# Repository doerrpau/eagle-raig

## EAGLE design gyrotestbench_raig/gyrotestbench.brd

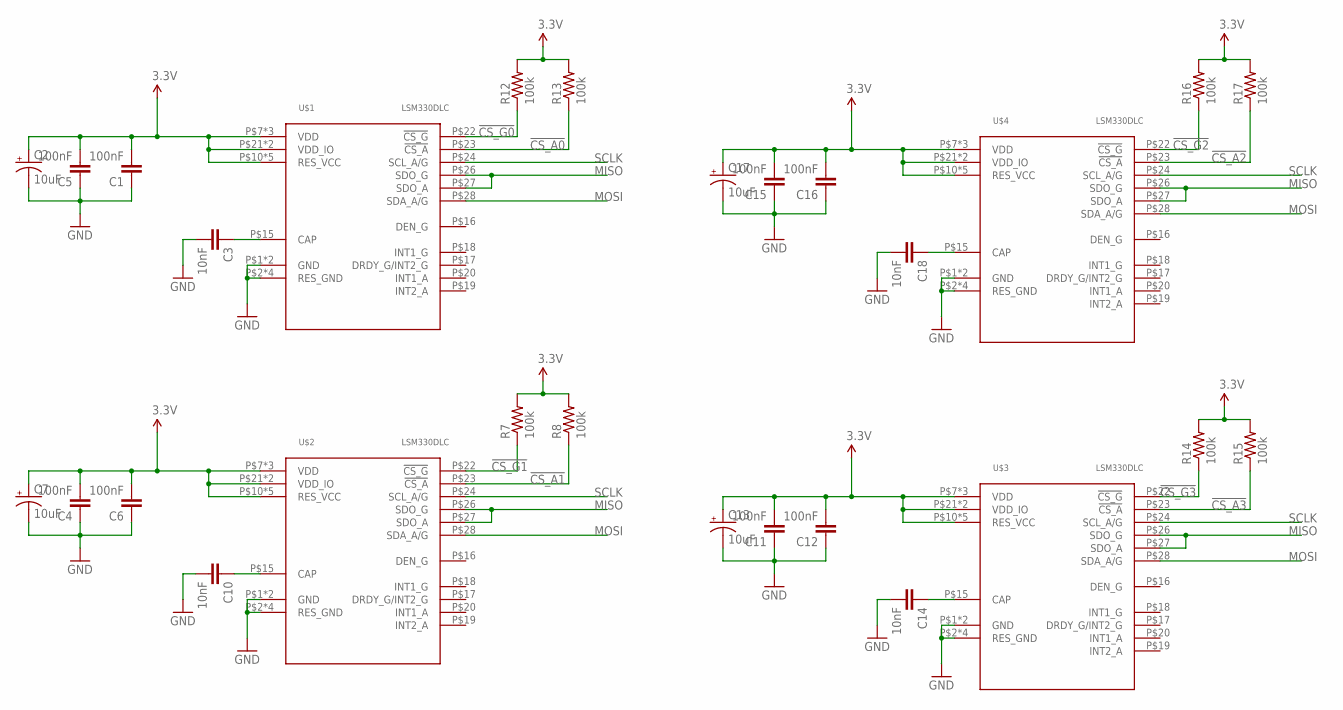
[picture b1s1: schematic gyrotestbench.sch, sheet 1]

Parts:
C1, C4, C5, C6, C11, C12, C15, C16: 100nF; 0603-CAP
C2, C7, C13, C17: 10uF; PANASONIC_B
C3, C10, C14, C18: 10nF; 0603-CAP
R7, R8, R12, R13, R14, R15, R16, R17: 100k; 0603-RES
U$1, U$2, U$3, U$4: LSM330DLC; LGA-28

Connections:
3.3V: C1.2, C2.+, C4.2, C5.2, C6.2, C7.+, C11.2, C12.2, C13.+, C15.2, C16.2, C17.+, R7.2, R8.2, R12.2, R13.2, R14.2, R15.2, R16.2, R17.2, U$1.P$7 (VDD), U$1.P$8 (VDD), U$1.P$9 (VDD), U$1.P$10 (RES_VCC), U$1.P$11 (RES_VCC), U$1.P$12 (RES_VCC), U$1.P$13 (RES_VCC), U$1.P$14 (RES_VCC), U$1.P$21 (VDD_IO), U$1.P$25 (VDD_IO), U$2.P$7 (VDD), U$2.P$8 (VDD), U$2.P$9 (VDD), U$2.P$10 (RES_VCC), U$2.P$11 (RES_VCC), U$2.P$12 (RES_VCC), U$2.P$13 (RES_VCC), U$2.P$14 (RES_VCC), U$2.P$21 (VDD_IO), U$2.P$25 (VDD_IO), U$3.P$7 (VDD), U$3.P$8 (VDD), U$3.P$9 (VDD), U$3.P$10 (RES_VCC), U$3.P$11 (RES_VCC), U$3.P$12 (RES_VCC), U$3.P$13 (RES_VCC), U$3.P$14 (RES_VCC), U$3.P$21 (VDD_IO), U$3.P$25 (VDD_IO), U$4.P$7 (VDD), U$4.P$8 (VDD), U$4.P$9 (VDD), U$4.P$10 (RES_VCC), U$4.P$11 (RES_VCC), U$4.P$12 (RES_VCC), U$4.P$13 (RES_VCC), U$4.P$14 (RES_VCC), U$4.P$21 (VDD_IO), U$4.P$25 (VDD_IO); also elsewhere on the board
!CS_A0: R13.1, U$1.P$23 (!CS_A); also elsewhere on the board
!CS_A1: R8.1, U$2.P$23 (!CS_A); also elsewhere on the board
!CS_A2: R17.1, U$4.P$23 (!CS_A); also elsewhere on the board
!CS_A3: R15.1, U$3.P$23 (!CS_A); also elsewhere on the board
!CS_G0: R12.1, U$1.P$22 (!CS_G); also elsewhere on the board
!CS_G1: R7.1, U$2.P$22 (!CS_G); also elsewhere on the board
!CS_G2: R16.1, U$4.P$22 (!CS_G); also elsewhere on the board
!CS_G3: R14.1, U$3.P$22 (!CS_G); also elsewhere on the board
GND: C1.1, C2.-, C3.2, C4.1, C5.1, C6.1, C7.-, C10.2, C11.1, C12.1, C13.-, C14.2, C15.1, C16.1, C17.-, C18.2, U$1.P$1 (GND), U$1.P$2 (RES_GND), U$1.P$3 (RES_GND), U$1.P$4 (RES_GND), U$1.P$5 (RES_GND), U$1.P$6 (GND), U$2.P$1 (GND), U$2.P$2 (RES_GND), U$2.P$3 (RES_GND), U$2.P$4 (RES_GND), U$2.P$5 (RES_GND), U$2.P$6 (GND), U$3.P$1 (GND), U$3.P$2 (RES_GND), U$3.P$3 (RES_GND), U$3.P$4 (RES_GND), U$3.P$5 (RES_GND), U$3.P$6 (GND), U$4.P$1 (GND), U$4.P$2 (RES_GND), U$4.P$3 (RES_GND), U$4.P$4 (RES_GND), U$4.P$5 (RES_GND), U$4.P$6 (GND); also elsewhere on the board
MISO: U$1.P$26 (SDO_G), U$1.P$27 (SDO_A), U$2.P$26 (SDO_G), U$2.P$27 (SDO_A), U$3.P$26 (SDO_G), U$3.P$27 (SDO_A), U$4.P$26 (SDO_G), U$4.P$27 (SDO_A); also elsewhere on the board
MOSI: U$1.P$28 (SDA_A/G), U$2.P$28 (SDA_A/G), U$3.P$28 (SDA_A/G), U$4.P$28 (SDA_A/G); also elsewhere on the board
unnamed: C3.1, U$1.P$15 (CAP)
unnamed: C10.1, U$2.P$15 (CAP)
unnamed: C14.1, U$3.P$15 (CAP)
unnamed: C18.1, U$4.P$15 (CAP)
SCLK: U$1.P$24 (SCL_A/G), U$2.P$24 (SCL_A/G), U$3.P$24 (SCL_A/G), U$4.P$24 (SCL_A/G); also elsewhere on the board

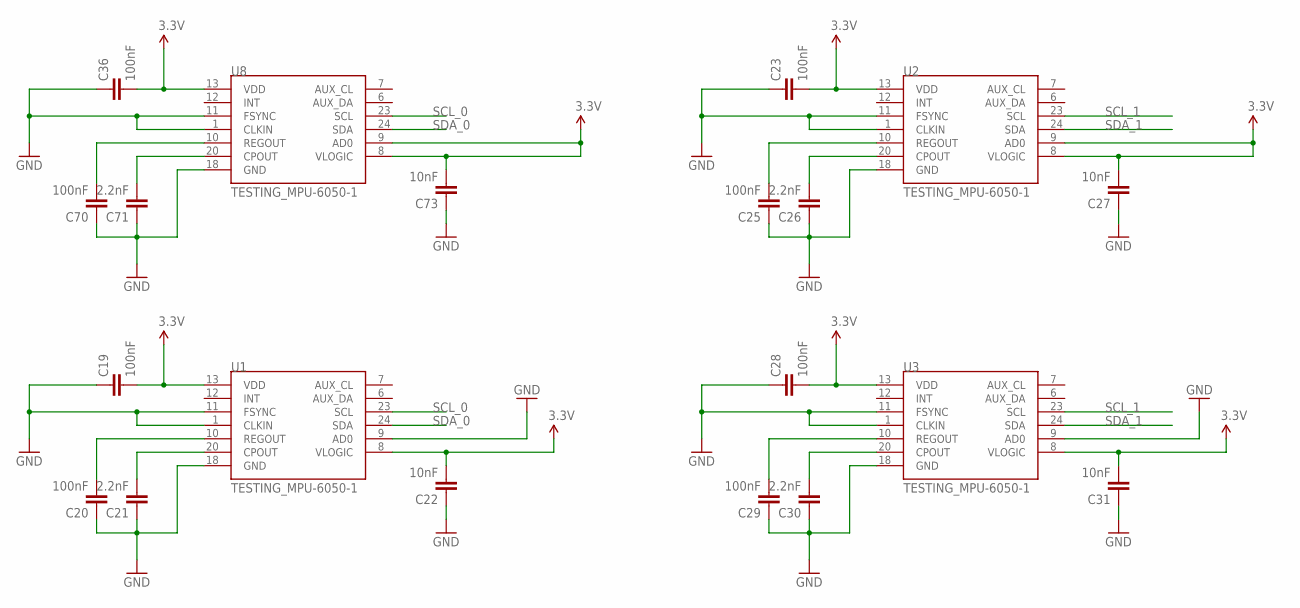
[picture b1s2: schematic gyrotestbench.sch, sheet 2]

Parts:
C19, C20, C23, C25, C28, C29, C36, C70: 100nF; 0603-CAP
C21, C26, C30, C71: 2.2nF; 0603-CAP
C22, C27, C31, C73: 10nF; 0603-CAP
U1, U2, U3, U8: TESTING_MPU-6050-1; TESTING_QFN-24-4MM2

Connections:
3.3V: C19.2, C22.2, C23.2, C27.2, C28.2, C31.2, C36.2, C73.2, U1.8 (VLOGIC), U1.13 (VDD), U2.8 (VLOGIC), U2.9 (AD0), U2.13 (VDD), U3.8 (VLOGIC), U3.13 (VDD), U8.8 (VLOGIC), U8.9 (AD0), U8.13 (VDD); also elsewhere on the board
GND: C19.1, C20.1, C21.1, C22.1, C23.1, C25.1, C26.1, C27.1, C28.1, C29.1, C30.1, C31.1, C36.1, C70.1, C71.1, C73.1, U1.1 (CLKIN), U1.9 (AD0), U1.11 (FSYNC), U1.18 (GND), U2.1 (CLKIN), U2.11 (FSYNC), U2.18 (GND), U3.1 (CLKIN), U3.9 (AD0), U3.11 (FSYNC), U3.18 (GND), U8.1 (CLKIN), U8.11 (FSYNC), U8.18 (GND); also elsewhere on the board
unnamed: C20.2, U1.10 (REGOUT)
unnamed: C21.2, U1.20 (CPOUT)
unnamed: C25.2, U2.10 (REGOUT)
unnamed: C26.2, U2.20 (CPOUT)
unnamed: C29.2, U3.10 (REGOUT)
unnamed: C30.2, U3.20 (CPOUT)
unnamed: C70.2, U8.10 (REGOUT)
unnamed: C71.2, U8.20 (CPOUT)
SCL_0: U1.23 (SCL), U8.23 (SCL); also elsewhere on the board
SCL_1: U2.23 (SCL), U3.23 (SCL); also elsewhere on the board
SDA_0: U1.24 (SDA), U8.24 (SDA); also elsewhere on the board
SDA_1: U2.24 (SDA), U3.24 (SDA); also elsewhere on the board

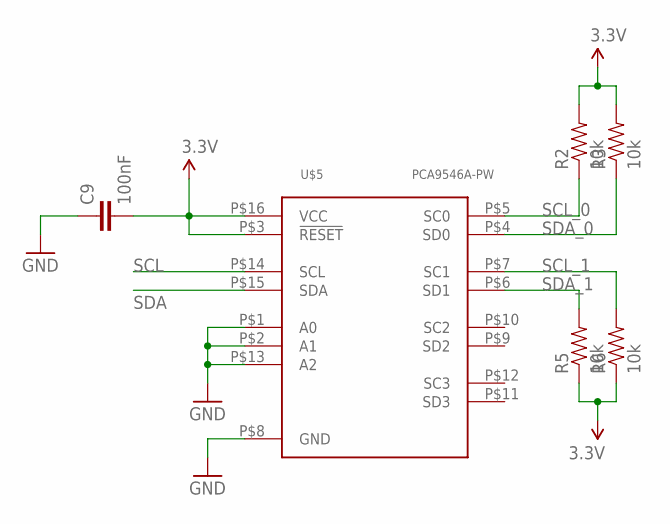
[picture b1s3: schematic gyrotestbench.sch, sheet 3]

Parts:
C9: 100nF; 0603-CAP
R2, R3, R5, R6: 10k; 0603-RES
U$5: PCA9546A-PW; TSSOP-16

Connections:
3.3V: C9.2, R2.2, R3.2, R5.1, R6.1, U$5.P$3 (!RESET), U$5.P$16 (VCC); also elsewhere on the board
GND: C9.1, U$5.P$1 (A0), U$5.P$2 (A1), U$5.P$8 (GND), U$5.P$13 (A2); also elsewhere on the board
SCL: U$5.P$14 (SCL); also elsewhere on the board
SCL_0: R2.1, U$5.P$5 (SC0); also elsewhere on the board
SCL_1: R6.2, U$5.P$7 (SC1); also elsewhere on the board
SDA: U$5.P$15 (SDA); also elsewhere on the board
SDA_0: R3.1, U$5.P$4 (SD0); also elsewhere on the board
SDA_1: R5.2, U$5.P$6 (SD1); also elsewhere on the board

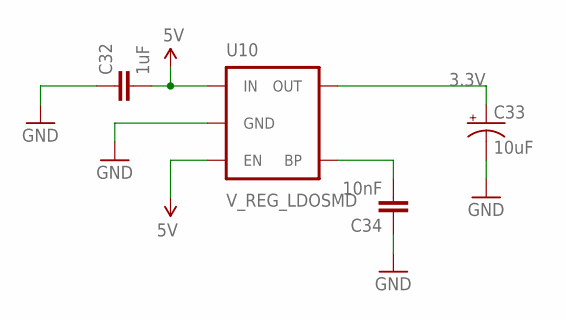
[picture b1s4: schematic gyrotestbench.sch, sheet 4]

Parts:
C32: 1uF; 0603-CAP
C33: 10uF; PANASONIC_B
C34: 10nF; 0603-CAP
U10: V_REG_LDOSMD; SOT23-5

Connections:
3.3V: C33.+, U10.5 (OUT); also elsewhere on the board
5V: C32.2, U10.1 (IN), U10.3 (EN); also elsewhere on the board
GND: C32.1, C33.-, C34.1, U10.2 (GND); also elsewhere on the board
unnamed: C34.2, U10.4 (BP)

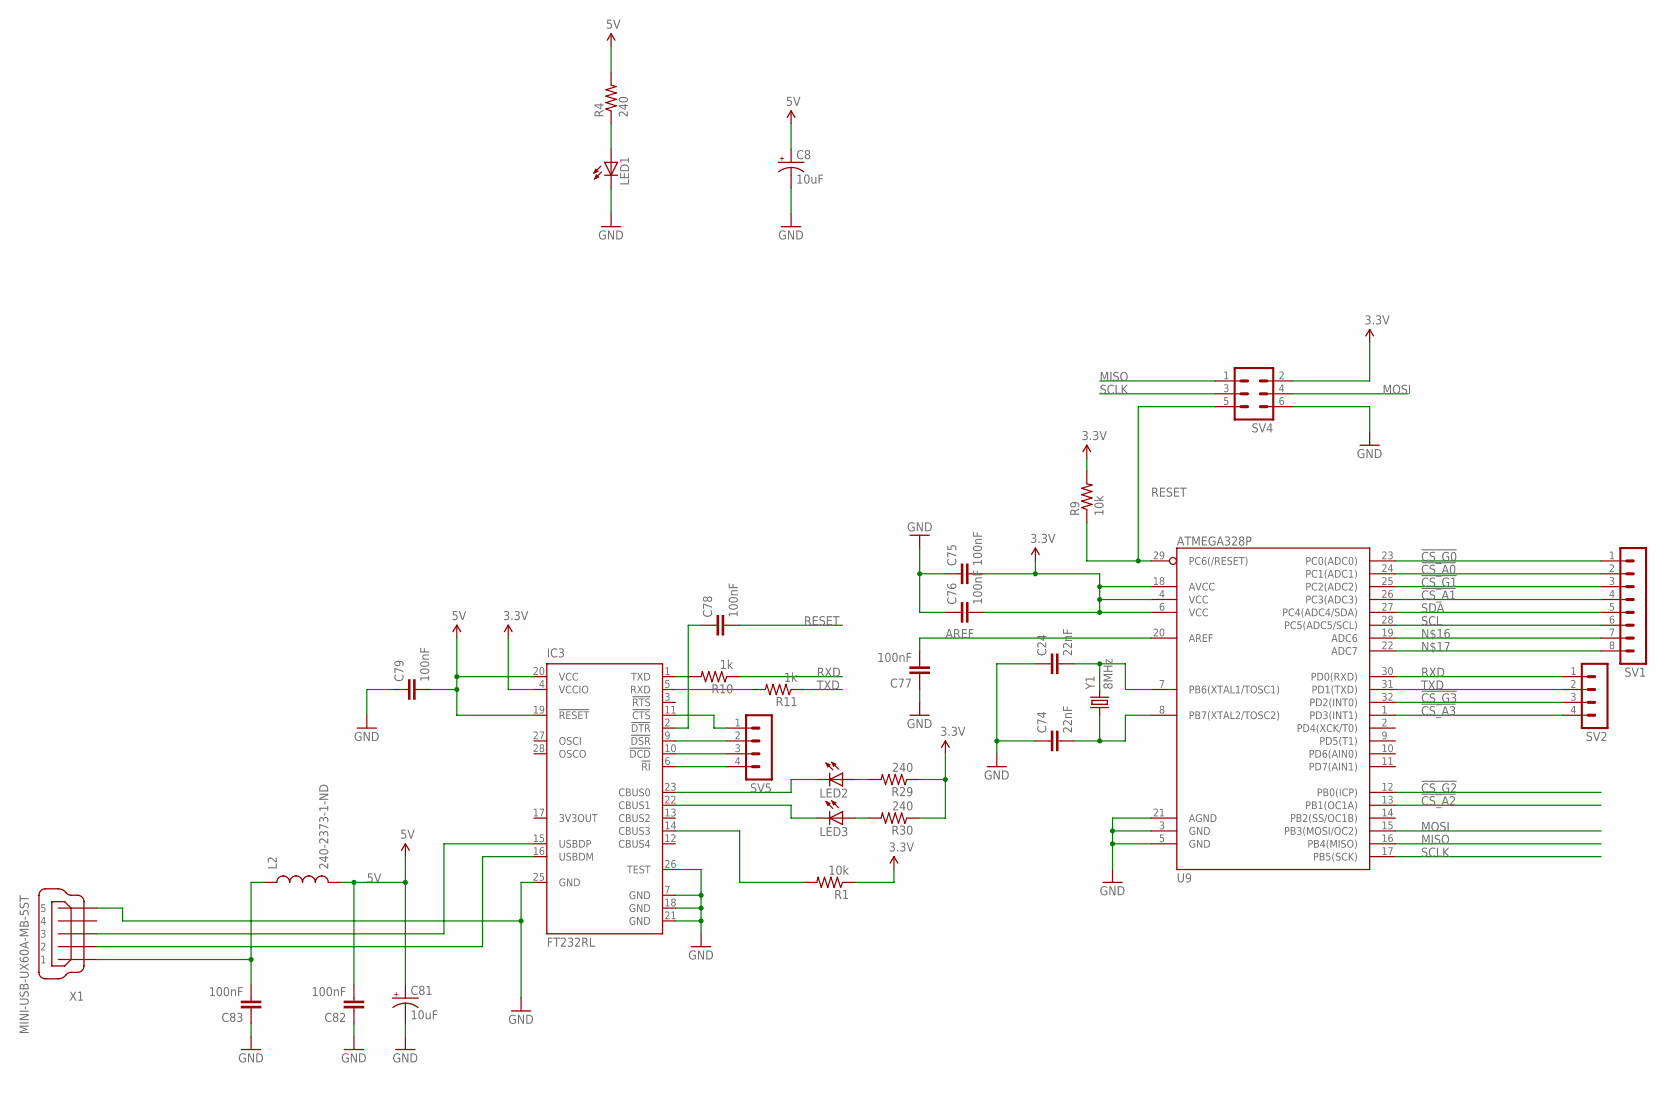
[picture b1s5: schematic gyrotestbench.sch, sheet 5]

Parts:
C8, C81: 10uF; PANASONIC_B
C24, C74: 22nF; 0603-CAP
C75, C76, C77, C78, C79, C82, C83: 100nF; 0603-CAP
IC3: FT232RL; SSOP28
L2: 240-2373-1-ND; 0603
LED1, LED2, LED3: LED0603; LED-0603
R1, R9: 10k; 0603-RES
R4, R29, R30: 240; 0603-RES
R10, R11: 1k; 0603-RES
SV1: MA08-1
SV2, SV5: MA04-1
SV4: MA03-2
U9: ATMEGA328P; TQFP32-08
X1: MINI-USB-UX60A-MB-5ST; UX60A-MB-5ST
Y1: 8MHz; HC49US

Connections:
3.3V: C75.2, C76.2, IC3.4 (VCCIO), R1.1, R9.2, R29.1, R30.1, SV4.2, U9.4 (VCC), U9.6 (VCC), U9.18 (AVCC); also elsewhere on the board
5V: C8.+, C79.2, C81.+, C82.2, IC3.19 (!RESET), IC3.20 (VCC), L2.2, R4.2; also elsewhere on the board
!CS_A0: SV1.2, U9.24 (PC1(ADC1)); also elsewhere on the board
!CS_A1: SV1.4, U9.26 (PC3(ADC3)); also elsewhere on the board
!CS_A2: U9.13 (PB1(OC1A)); also elsewhere on the board
!CS_A3: SV2.4, U9.1 (PD3(INT1)); also elsewhere on the board
!CS_G0: SV1.1, U9.23 (PC0(ADC0)); also elsewhere on the board
!CS_G1: SV1.3, U9.25 (PC2(ADC2)); also elsewhere on the board
!CS_G2: U9.12 (PB0(ICP)); also elsewhere on the board
!CS_G3: SV2.3, U9.32 (PD2(INT0)); also elsewhere on the board
AREF: C77.2, U9.20 (AREF)
GND: C8.-, C24.1, C74.1, C75.1, C76.1, C77.1, C79.1, C81.-, C82.1, C83.1, IC3.7 (GND), IC3.18 (GND), IC3.21 (GND), IC3.25 (GND), IC3.26 (TEST), LED1.C, SV4.6, U9.3 (GND), U9.5 (GND), U9.21 (AGND), X1.5; also elsewhere on the board
MISO: SV4.1, U9.16 (PB4(MISO)); also elsewhere on the board
MOSI: SV4.4, U9.15 (PB3(MOSI/OC2)); also elsewhere on the board
unnamed: IC3.14 (CBUS3), R1.2
unnamed: IC3.15 (USBDP), X1.3
unnamed: C83.2, L2.1, X1.1
unnamed: IC3.16 (USBDM), X1.2
unnamed: SV1.7, U9.19 (ADC6)
unnamed: SV1.8, U9.22 (ADC7)
unnamed: IC3.1 (TXD), R10.2
unnamed: C78.1, IC3.2 (!DTR)
unnamed: IC3.5 (RXD), R11.2
unnamed: IC3.11 (!CTS), SV5.1
unnamed: IC3.9 (!DSR), SV5.2
unnamed: C24.2, U9.7 (PB6(XTAL1/TOSC1)), Y1.2
unnamed: C74.2, U9.8 (PB7(XTAL2/TOSC2)), Y1.1
unnamed: LED1.A, R4.1
unnamed: IC3.10 (!DCD), SV5.3
unnamed: IC3.6 (!RI), SV5.4
unnamed: IC3.23 (CBUS0), LED2.C
unnamed: IC3.22 (CBUS1), LED3.C
unnamed: LED2.A, R29.2
unnamed: LED3.A, R30.2
RESET: C78.2, R9.1, SV4.5, U9.29 (PC6(/RESET))
RXD: R10.1, SV2.1, U9.30 (PD0(RXD))
SCL: SV1.6, U9.28 (PC5(ADC5/SCL)); also elsewhere on the board
SCLK: SV4.3, U9.17 (PB5(SCK)); also elsewhere on the board
SDA: SV1.5, U9.27 (PC4(ADC4/SDA)); also elsewhere on the board
TXD: R11.1, SV2.2, U9.31 (PD1(TXD))

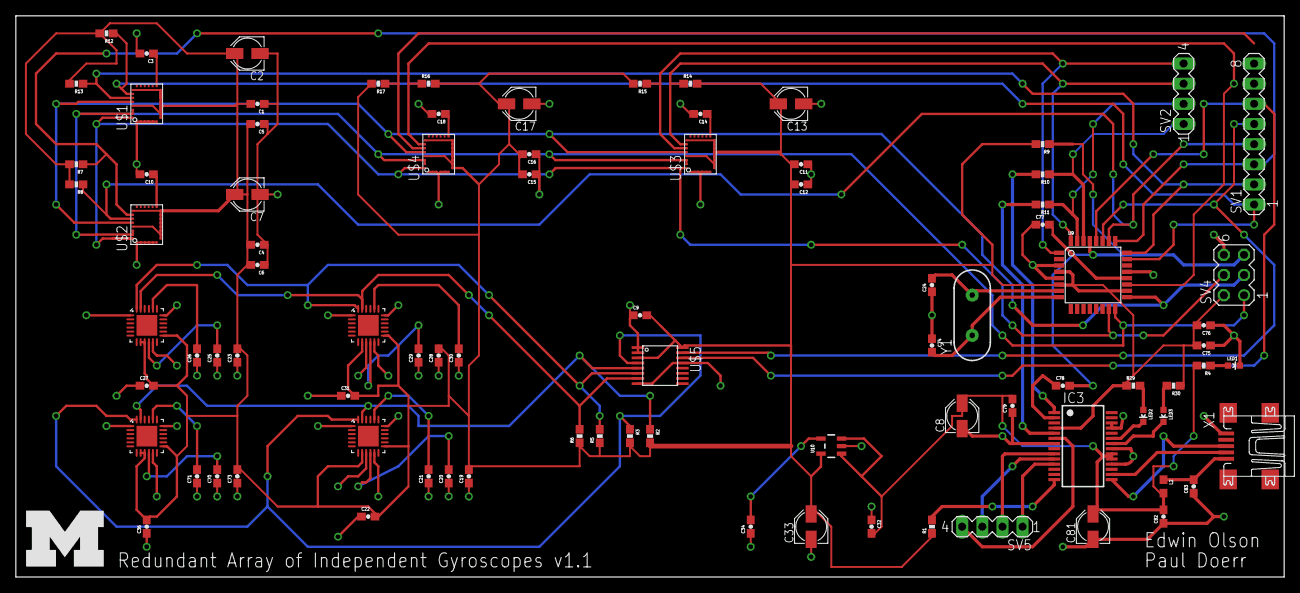
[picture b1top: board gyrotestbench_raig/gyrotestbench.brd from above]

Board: 2 copper layers, 160.0 x 70.8 mm, 89 parts (0 on the bottom side), 57 nets.

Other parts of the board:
U$6: BLOCK_M

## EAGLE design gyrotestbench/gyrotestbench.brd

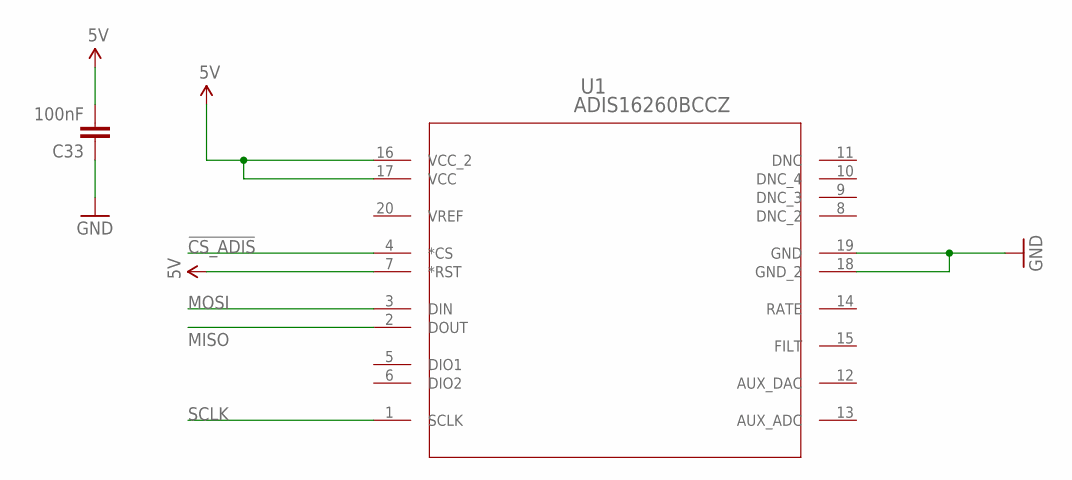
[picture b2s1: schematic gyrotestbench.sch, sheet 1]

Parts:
C33: 100nF; 0603-CAP
U1: ADIS16260BCCZ; LGA_CC-20-1

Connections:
5V: C33.2, U1.7 (*RST), U1.16 (VCC_2), U1.17 (VCC); also elsewhere on the board
!CS_ADIS: U1.4 (*CS); also elsewhere on the board
GND: C33.1, U1.18 (GND_2), U1.19 (GND); also elsewhere on the board
MISO: U1.2 (DOUT); also elsewhere on the board
MOSI: U1.3 (DIN); also elsewhere on the board
SCLK: U1.1 (SCLK); also elsewhere on the board

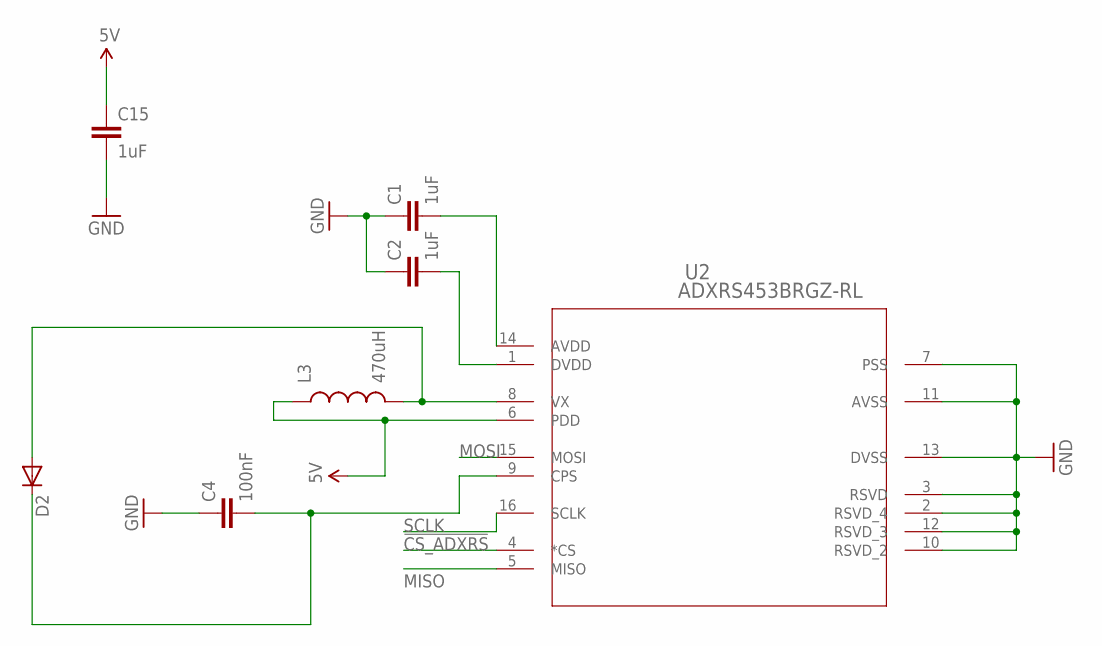
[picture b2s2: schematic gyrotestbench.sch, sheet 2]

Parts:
C1, C2, C15: 1uF; 0603-CAP
C4: 100nF; 0603-CAP
D2: DIODEPTH; DIODE-1N4001
L3: 470uH; 1210
U2: ADXRS453BRGZ-RL; RG_16_1

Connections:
5V: C15.1, L3.1, U2.6 (PDD); also elsewhere on the board
!CS_ADXRS: U2.4 (*CS); also elsewhere on the board
GND: C1.1, C2.1, C4.1, C15.2, U2.2 (RSVD_4), U2.3 (RSVD), U2.7 (PSS), U2.10 (RSVD_2), U2.11 (AVSS), U2.12 (RSVD_3), U2.13 (DVSS); also elsewhere on the board
MISO: U2.5 (MISO); also elsewhere on the board
MOSI: U2.15 (MOSI); also elsewhere on the board
unnamed: C1.2, U2.14 (AVDD)
unnamed: C2.2, U2.1 (DVDD)
unnamed: C4.2, D2.C, U2.9 (CPS)
unnamed: D2.A, L3.2, U2.8 (VX)
SCLK: U2.16 (SCLK); also elsewhere on the board

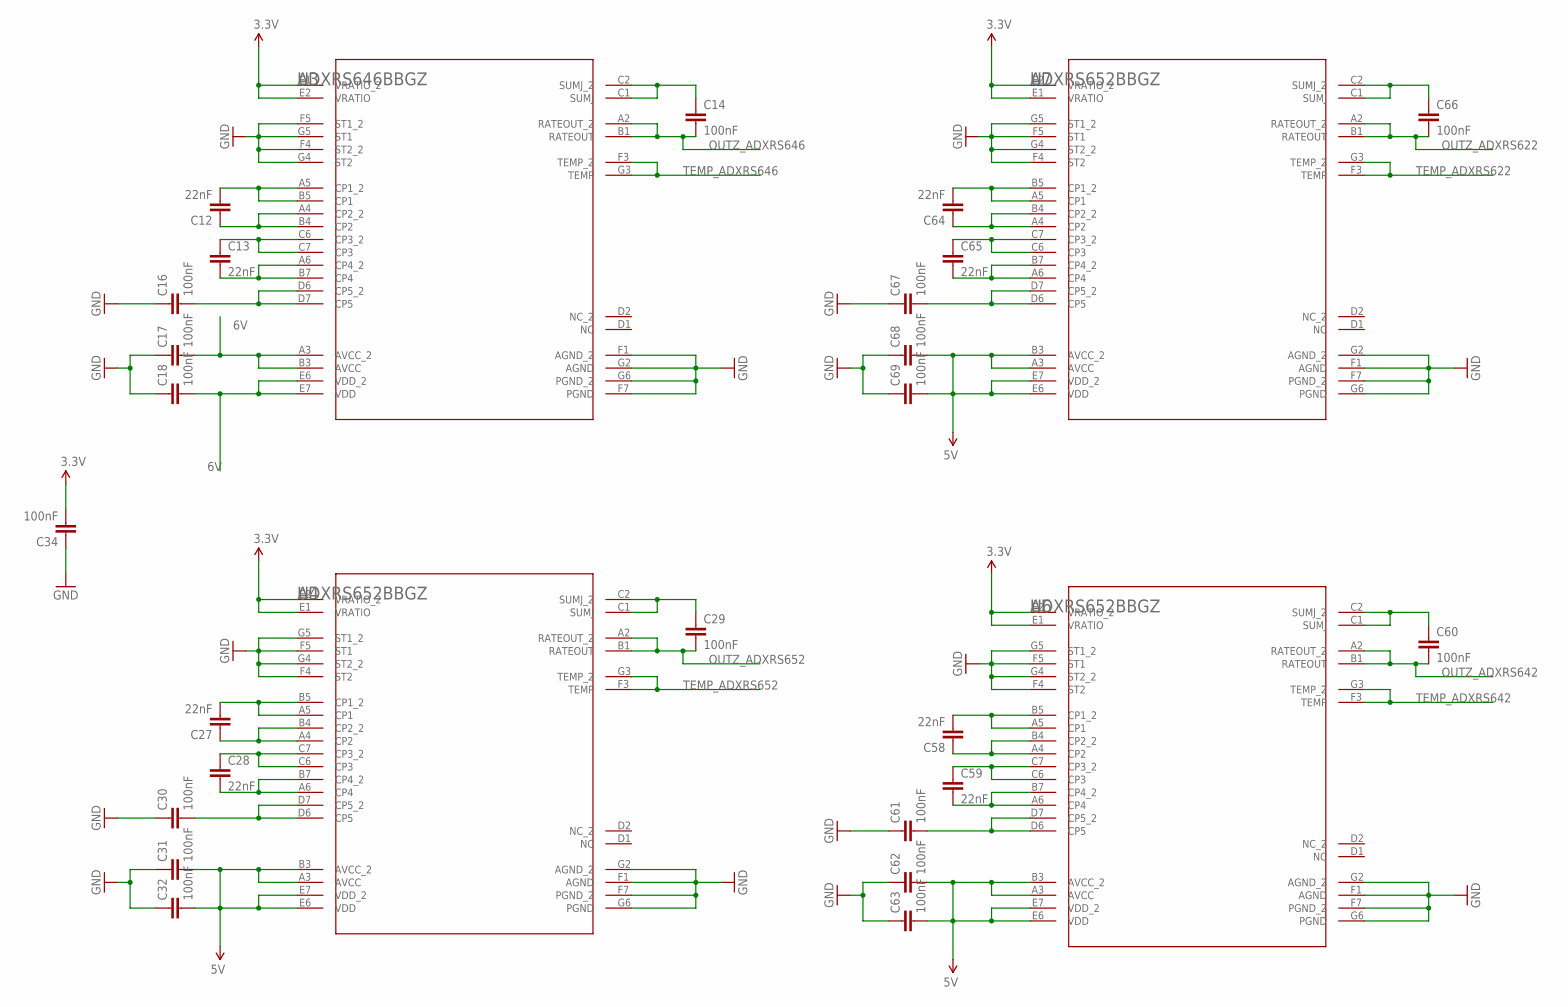
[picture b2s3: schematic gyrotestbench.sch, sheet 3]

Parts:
C12, C13, C27, C28, C58, C59, C64, C65: 22nF; 0603-CAP
C14, C16, C17, C18, C29, C30, C31, C32, C34, C60, C61, C62, C63, C66, C67, C68, C69: 100nF; 0603-CAP
U3: ADXRS646BBGZ; BG_32_3
U4, U6, U7: ADXRS652BBGZ; BG_32_3

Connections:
3.3V: C34.2, U3.E1 (VRATIO_2), U3.E2 (VRATIO), U4.E1 (VRATIO), U4.E2 (VRATIO_2), U6.E1 (VRATIO), U6.E2 (VRATIO_2), U7.E1 (VRATIO), U7.E2 (VRATIO_2); also elsewhere on the board
5V: C31.2, C32.2, C62.2, C63.2, C68.2, C69.2, U4.A3 (AVCC), U4.B3 (AVCC_2), U4.E6 (VDD), U4.E7 (VDD_2), U6.A3 (AVCC), U6.B3 (AVCC_2), U6.E6 (VDD), U6.E7 (VDD_2), U7.A3 (AVCC), U7.B3 (AVCC_2), U7.E6 (VDD), U7.E7 (VDD_2); also elsewhere on the board
6V: C17.2, C18.2, U3.A3 (AVCC_2), U3.B3 (AVCC), U3.E6 (VDD_2), U3.E7 (VDD); also elsewhere on the board
GND: C16.1, C17.1, C18.1, C30.1, C31.1, C32.1, C34.1, C61.1, C62.1, C63.1, C67.1, C68.1, C69.1, U3.F1 (AGND_2), U3.F4 (ST2_2), U3.F5 (ST1_2), U3.F7 (PGND), U3.G2 (AGND), U3.G4 (ST2), U3.G5 (ST1), U3.G6 (PGND_2), U4.F1 (AGND), U4.F4 (ST2), U4.F5 (ST1), U4.F7 (PGND_2), U4.G2 (AGND_2), U4.G4 (ST2_2), U4.G5 (ST1_2), U4.G6 (PGND), U6.F1 (AGND), U6.F4 (ST2), U6.F5 (ST1), U6.F7 (PGND_2), U6.G2 (AGND_2), U6.G4 (ST2_2), U6.G5 (ST1_2), U6.G6 (PGND), U7.F1 (AGND), U7.F4 (ST2), U7.F5 (ST1), U7.F7 (PGND_2), U7.G2 (AGND_2), U7.G4 (ST2_2), U7.G5 (ST1_2), U7.G6 (PGND); also elsewhere on the board
unnamed: C12.2, U3.A5 (CP1_2), U3.B5 (CP1)
unnamed: C12.1, U3.A4 (CP2_2), U3.B4 (CP2)
unnamed: C13.1, U3.C6 (CP3_2), U3.C7 (CP3)
unnamed: C13.2, U3.A6 (CP4_2), U3.B7 (CP4)
unnamed: C14.1, U3.C1 (SUMJ), U3.C2 (SUMJ_2)
unnamed: C16.2, U3.D6 (CP5_2), U3.D7 (CP5)
unnamed: C27.2, U4.A5 (CP1), U4.B5 (CP1_2)
unnamed: C27.1, U4.A4 (CP2), U4.B4 (CP2_2)
unnamed: C28.1, U4.C6 (CP3), U4.C7 (CP3_2)
unnamed: C28.2, U4.A6 (CP4), U4.B7 (CP4_2)
unnamed: C29.1, U4.C1 (SUMJ), U4.C2 (SUMJ_2)
unnamed: C30.2, U4.D6 (CP5), U4.D7 (CP5_2)
unnamed: C58.2, U6.A5 (CP1), U6.B5 (CP1_2)
unnamed: C58.1, U6.A4 (CP2), U6.B4 (CP2_2)
unnamed: C59.1, U6.C6 (CP3), U6.C7 (CP3_2)
unnamed: C59.2, U6.A6 (CP4), U6.B7 (CP4_2)
unnamed: C60.1, U6.C1 (SUMJ), U6.C2 (SUMJ_2)
unnamed: C61.2, U6.D6 (CP5), U6.D7 (CP5_2)
unnamed: C64.2, U7.A5 (CP1), U7.B5 (CP1_2)
unnamed: C64.1, U7.A4 (CP2), U7.B4 (CP2_2)
unnamed: C65.1, U7.C6 (CP3), U7.C7 (CP3_2)
unnamed: C65.2, U7.A6 (CP4), U7.B7 (CP4_2)
unnamed: C66.1, U7.C1 (SUMJ), U7.C2 (SUMJ_2)
unnamed: C67.2, U7.D6 (CP5), U7.D7 (CP5_2)
OUTZ_ADXRS622: C66.2, U7.A2 (RATEOUT_2), U7.B1 (RATEOUT); also elsewhere on the board
OUTZ_ADXRS642: C60.2, U6.A2 (RATEOUT_2), U6.B1 (RATEOUT); also elsewhere on the board
OUTZ_ADXRS646: C14.2, U3.A2 (RATEOUT_2), U3.B1 (RATEOUT); also elsewhere on the board
OUTZ_ADXRS652: C29.2, U4.A2 (RATEOUT_2), U4.B1 (RATEOUT); also elsewhere on the board
TEMP_ADXRS622: U7.F3 (TEMP), U7.G3 (TEMP_2); also elsewhere on the board
TEMP_ADXRS642: U6.F3 (TEMP), U6.G3 (TEMP_2); also elsewhere on the board
TEMP_ADXRS646: U3.F3 (TEMP_2), U3.G3 (TEMP); also elsewhere on the board
TEMP_ADXRS652: U4.F3 (TEMP), U4.G3 (TEMP_2); also elsewhere on the board

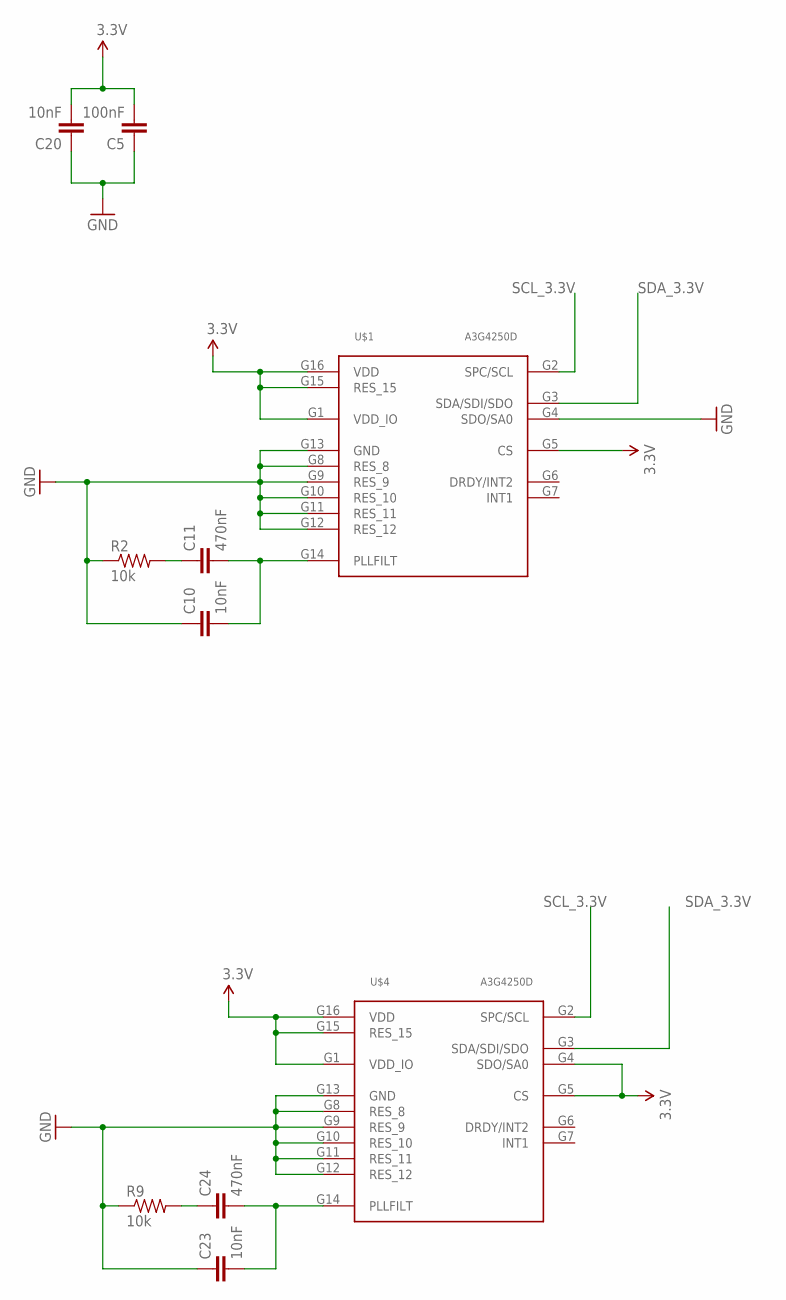
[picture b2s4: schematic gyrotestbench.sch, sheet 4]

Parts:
C5: 100nF; 0603-CAP
C10, C20, C23: 10nF; 0603-CAP
C11, C24: 470nF; 0603-CAP
R2, R9: 10k; 0603-RES
U$1, U$4: A3G4250D; LGA-16

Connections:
3.3V: C5.2, C20.2, U$1.G1 (VDD_IO), U$1.G5 (CS), U$1.G15 (RES_15), U$1.G16 (VDD), U$4.G1 (VDD_IO), U$4.G4 (SDO/SA0), U$4.G5 (CS), U$4.G15 (RES_15), U$4.G16 (VDD); also elsewhere on the board
GND: C5.1, C10.1, C20.1, C23.1, R2.1, R9.1, U$1.G4 (SDO/SA0), U$1.G8 (RES_8), U$1.G9 (RES_9), U$1.G10 (RES_10), U$1.G11 (RES_11), U$1.G12 (RES_12), U$1.G13 (GND), U$4.G8 (RES_8), U$4.G9 (RES_9), U$4.G10 (RES_10), U$4.G11 (RES_11), U$4.G12 (RES_12), U$4.G13 (GND); also elsewhere on the board
unnamed: C10.2, C11.2, U$1.G14 (PLLFILT)
unnamed: C11.1, R2.2
unnamed: C23.2, C24.2, U$4.G14 (PLLFILT)
unnamed: C24.1, R9.2
SCL_3.3V: U$1.G2 (SPC/SCL), U$4.G2 (SPC/SCL); also elsewhere on the board
SDA_3.3V: U$1.G3 (SDA/SDI/SDO), U$4.G3 (SDA/SDI/SDO); also elsewhere on the board

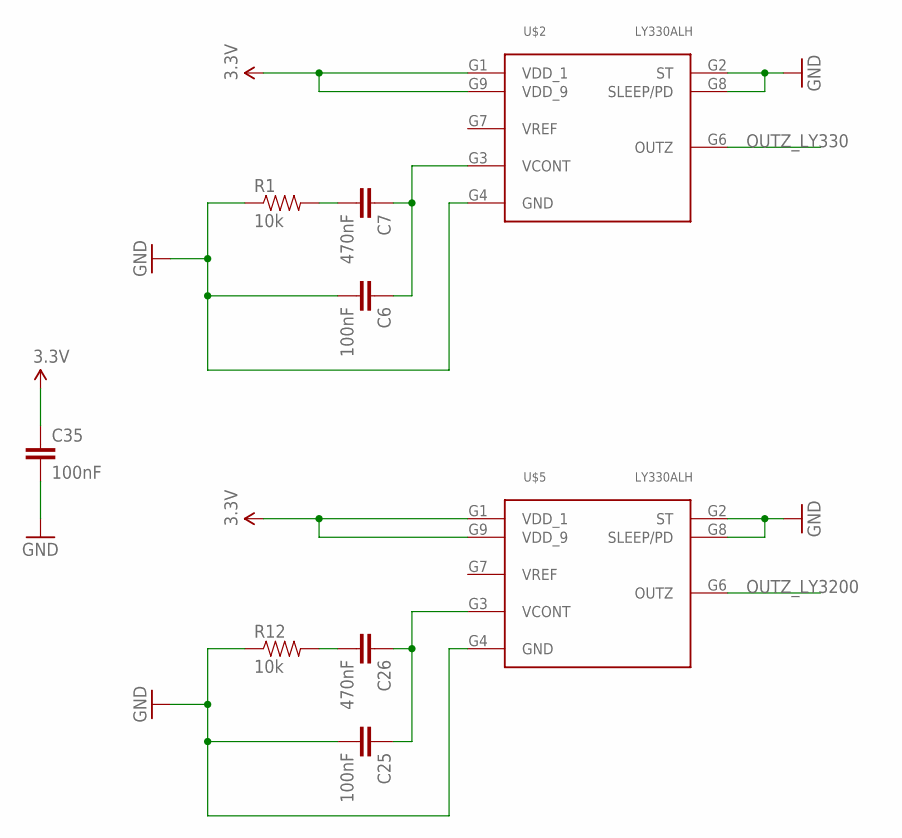
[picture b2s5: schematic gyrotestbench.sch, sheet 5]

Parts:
C6, C25, C35: 100nF; 0603-CAP
C7, C26: 470nF; 0603-CAP
R1, R12: 10k; 0603-RES
U$2, U$5: LY330ALH; LGA-10

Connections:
3.3V: C35.1, U$2.G1 (VDD_1), U$2.G9 (VDD_9), U$5.G1 (VDD_1), U$5.G9 (VDD_9); also elsewhere on the board
GND: C6.2, C25.2, C35.2, R1.1, R12.1, U$2.G2 (ST), U$2.G4 (GND), U$2.G8 (SLEEP/PD), U$5.G2 (ST), U$5.G4 (GND), U$5.G8 (SLEEP/PD); also elsewhere on the board
unnamed: C7.2, R1.2
unnamed: C6.1, C7.1, U$2.G3 (VCONT)
unnamed: C25.1, C26.1, U$5.G3 (VCONT)
unnamed: C26.2, R12.2
OUTZ_LY330: U$2.G6 (OUTZ); also elsewhere on the board
OUTZ_LY3200: U$5.G6 (OUTZ); also elsewhere on the board

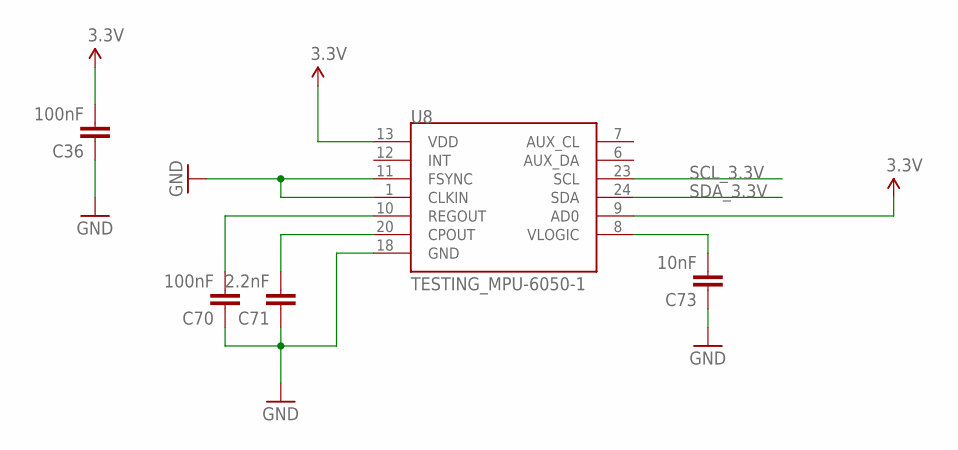
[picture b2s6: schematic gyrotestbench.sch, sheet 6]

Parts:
C36, C70: 100nF; 0603-CAP
C71: 2.2nF; 0603-CAP
C73: 10nF; 0603-CAP
U8: TESTING_MPU-6050-1; TESTING_QFN-24-4MM2

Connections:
3.3V: C36.2, U8.9 (AD0), U8.13 (VDD); also elsewhere on the board
GND: C36.1, C70.1, C71.1, C73.1, U8.1 (CLKIN), U8.11 (FSYNC), U8.18 (GND); also elsewhere on the board
unnamed: C70.2, U8.10 (REGOUT)
unnamed: C71.2, U8.20 (CPOUT)
unnamed: C73.2, U8.8 (VLOGIC)
SCL_3.3V: U8.23 (SCL); also elsewhere on the board
SDA_3.3V: U8.24 (SDA); also elsewhere on the board

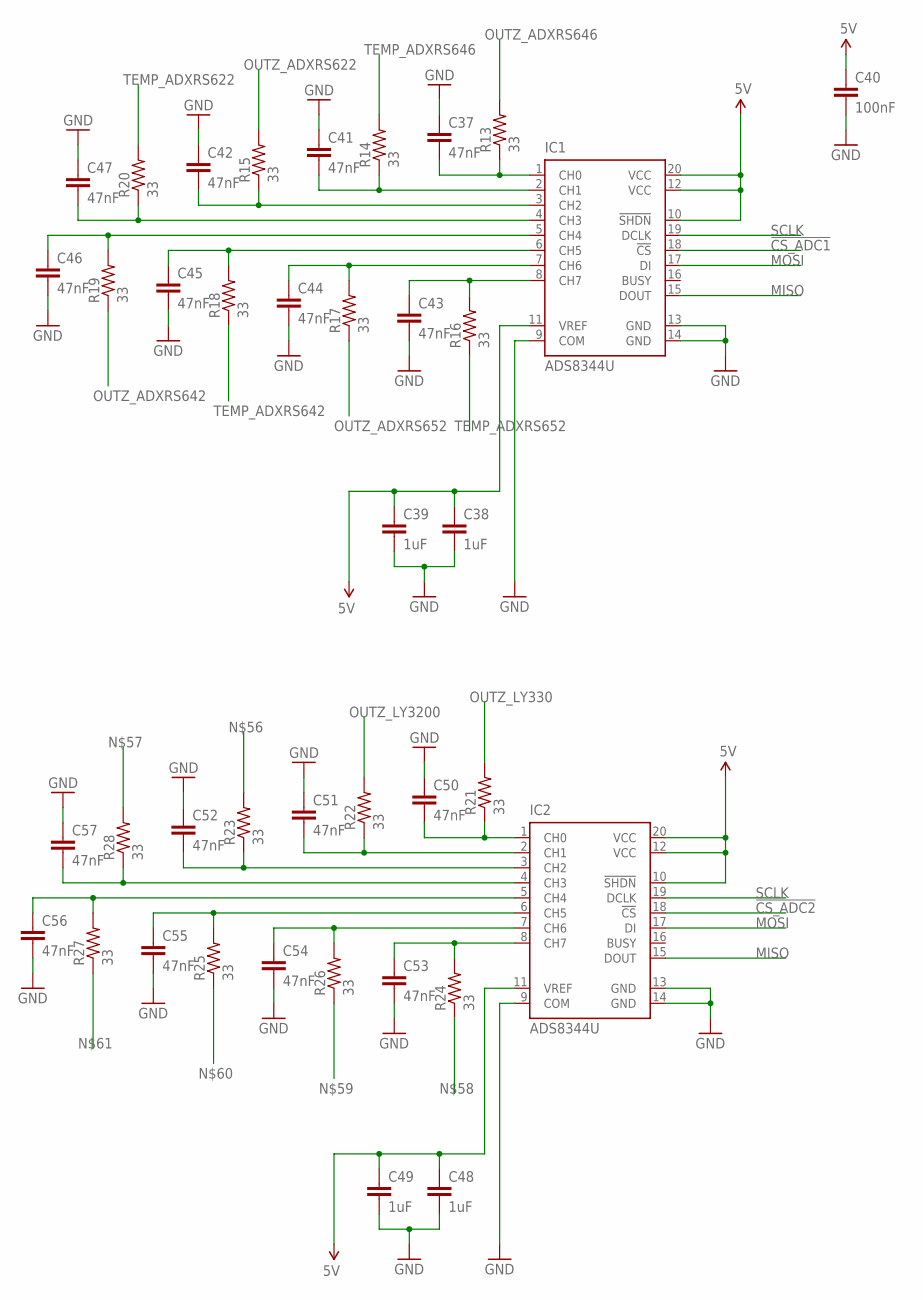
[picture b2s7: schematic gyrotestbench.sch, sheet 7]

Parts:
C37, C41, C42, C43, C44, C45, C46, C47, C50, C51, C52, C53, C54, C55, C56, C57: 47nF; 0603-CAP
C38, C39, C48, C49: 1uF; 0603-CAP
C40: 100nF; 0603-CAP
IC1, IC2: ADS8344U; SSOP20BU
R13, R14, R15, R16, R17, R18, R19, R20, R21, R22, R23, R24, R25, R26, R27, R28: 33; 0603-RES

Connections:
5V: C38.1, C39.1, C40.1, C48.1, C49.1, IC1.10 (!SHDN), IC1.11 (VREF), IC1.12 (VCC), IC1.20 (VCC), IC2.10 (!SHDN), IC2.11 (VREF), IC2.12 (VCC), IC2.20 (VCC); also elsewhere on the board
!CS_ADC1: IC1.18 (!CS); also elsewhere on the board
!CS_ADC2: IC2.18 (!CS); also elsewhere on the board
GND: C37.1, C38.2, C39.2, C40.2, C41.1, C42.1, C43.2, C44.2, C45.2, C46.2, C47.1, C48.2, C49.2, C50.1, C51.1, C52.1, C53.2, C54.2, C55.2, C56.2, C57.1, IC1.9 (COM), IC1.13 (GND), IC1.14 (GND), IC2.9 (COM), IC2.13 (GND), IC2.14 (GND); also elsewhere on the board
MISO: IC1.15 (DOUT), IC2.15 (DOUT); also elsewhere on the board
MOSI: IC1.17 (DI), IC2.17 (DI); also elsewhere on the board
unnamed: C37.2, IC1.1 (CH0), R13.1
unnamed: C41.2, IC1.2 (CH1), R14.1
unnamed: C42.2, IC1.3 (CH2), R15.1
unnamed: C43.1, IC1.8 (CH7), R16.2
unnamed: C44.1, IC1.7 (CH6), R17.2
unnamed: C45.1, IC1.6 (CH5), R18.2
unnamed: C47.2, IC1.4 (CH3), R20.1
unnamed: C46.1, IC1.5 (CH4), R19.2
unnamed: C50.2, IC2.1 (CH0), R21.1
unnamed: C51.2, IC2.2 (CH1), R22.1
unnamed: C52.2, IC2.3 (CH2), R23.1
unnamed: C53.1, IC2.8 (CH7), R24.2
unnamed: C54.1, IC2.7 (CH6), R26.2
unnamed: C55.1, IC2.6 (CH5), R25.2
unnamed: C57.2, IC2.4 (CH3), R28.1
unnamed: C56.1, IC2.5 (CH4), R27.2
OUTZ_ADXRS622: R15.2; also elsewhere on the board
OUTZ_ADXRS642: R19.1; also elsewhere on the board
OUTZ_ADXRS646: R13.2; also elsewhere on the board
OUTZ_ADXRS652: R17.1; also elsewhere on the board
OUTZ_LY330: R21.2; also elsewhere on the board
OUTZ_LY3200: R22.2; also elsewhere on the board
SCLK: IC1.19 (DCLK), IC2.19 (DCLK); also elsewhere on the board
TEMP_ADXRS622: R20.2; also elsewhere on the board
TEMP_ADXRS642: R18.1; also elsewhere on the board
TEMP_ADXRS646: R14.2; also elsewhere on the board
TEMP_ADXRS652: R16.1; also elsewhere on the board

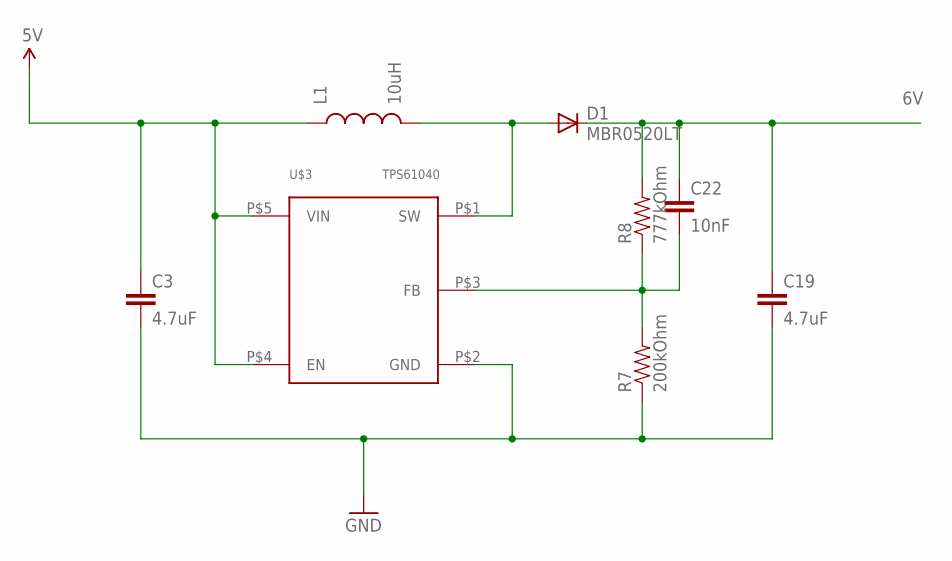
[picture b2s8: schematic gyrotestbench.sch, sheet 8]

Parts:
C3, C19: 4.7uF; 0603-CAP
C22: 10nF; 0603-CAP
D1: MBR0520LT; SOD123
L1: 10uH; 1210
R7: 200kOhm; 0603-RES
R8: 777kOhm; 0603-RES
U$3: TPS61040; DBV

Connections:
5V: C3.1, L1.1, U$3.P$4 (EN), U$3.P$5 (VIN); also elsewhere on the board
6V: C19.1, C22.1, D1.C, R8.2; also elsewhere on the board
GND: C3.2, C19.2, R7.1, U$3.P$2 (GND); also elsewhere on the board
unnamed: D1.A, L1.2, U$3.P$1 (SW)
unnamed: C22.2, R7.2, R8.1, U$3.P$3 (FB)

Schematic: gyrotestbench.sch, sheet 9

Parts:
C8, C9: CPOL-USB; PANASONIC_B
Q1, Q2: MOSFET-NCHANNELBSS138; SOT23
R5, R6, R31, R32: 10k; 0603-RES
U9: ARDUINO_SHIELDNO_SILK; DUEMILANOVE_VIAS

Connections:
3.3V: C9.+, Q1.1 (G), Q2.1 (G), R5.2, R31.2, U9.3.3V; also elsewhere on the board
5V: C8.+, R6.2, R32.2, U9.5V; also elsewhere on the board
!CS_ADC1: U9.D8; also elsewhere on the board
!CS_ADC2: U9.D9 (*D9); also elsewhere on the board
!CS_ADIS: U9.D6 (*D6); also elsewhere on the board
!CS_ADXRS: U9.D7; also elsewhere on the board
GND: C8.-, C9.-, U9.GND@0 (GND), U9.GND@1 (GND), U9.GND@2 (GND); also elsewhere on the board
MISO: U9.D12; also elsewhere on the board
MOSI: U9.D11 (*D11); also elsewhere on the board
SCLK: U9.D13; also elsewhere on the board
SCL_3.3V: Q2.2 (S), R31.1; also elsewhere on the board
SCL_5V: Q2.3 (D), R32.1, U9.A5
SDA_3.3V: Q1.2 (S), R5.1; also elsewhere on the board
SDA_5V: Q1.3 (D), R6.1, U9.A4

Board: 2 copper layers, 118 parts (0 on the bottom side), 82 nets, no tracks yet.

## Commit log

2013-04-29 Added current files
2013-05-10 Added arduino-based firmware
2013-05-11 Added java driver
2013-05-21 Firmware changes
2013-05-21 Severed RTS line on FTDI, added pull-ups to LSM chip select lines, and fixed silkscreen font
2013-05-31 Testing utilities
2013-06-07 Fixed interface problems, working on first stage IMU processing code
2013-06-10 Work on IMU code. Power Spectral Density and Angle Random Walk code added
2013-06-10 Standardized IMU methods
2013-06-11 Work on PSD/ARW/RRW. Started working on fused sensor calculations
2013-06-11 Finished fused sensor calculation code. Removed ARW/RRW code and instead added methods to convert from PSD to ARW/RRW.
2013-06-11 Cleaned up code; added acceleration and temperature processing
2013-06-11 Added (unused) gyro rate temperature sensitivity compensation
2013-06-11 Added gyroscope rate and fused rate processing
2013-06-12 Updated PSD testing utility
2013-09-12 Refactorized IMU code
2013-09-19 Refactorization and calibration code
2013-09-23 Added printing and logging files

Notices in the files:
parts and their libraries:
SparkFun-Capacitors: Licensing: CC v3.0 Share-Alike You are welcome to use this library for commercial purposes.
